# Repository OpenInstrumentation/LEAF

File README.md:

# LEAF
Logger for Environmental and Atmospheric Factors

CC-BY-SA 2019, A. Matheny, P. Marchetto, J. Powell, A. Rechner, J-y. Chuah, and S. Pierce

BoM: https://docs.google.com/spreadsheets/d/e/2PACX-1vQ8v-ukr38iTDn-cAedqp6OXnIay0lwoVsFbz_EMlWamA66PgREalaegVoSEzRlPvawVt73zznOhLpU/pubhtml or any of the BoM files above.

# Purpose
The LEAF is designed to be a modular sensing system, capable of measuring meteorological, hydrological, and other environmental parameters. In the design detailed in this repository, it was used to measure canopy throughfall of rain, soil moisture, and microclimate meteorological parameters, along with branch movement in the same tree the throughfall measurements were being made in.

# Files
The files in this repository are what's needed to program the different nodes of the sensing system network. The ground .ino file is different from the branches because it measures soil moisture as well; both of the .ino files are designed to be uploaded via Particle's online IDE at http://build.particle.io/. The catalog file includes all of the different items as priced at the time of the build, and the BoM includes direct links to them. The deployment file shows roughly what the initial instance looked like in its first deployment. The .brd and .sch files are Eagle board and schematic files, respectively, used to make PCBs for the system.

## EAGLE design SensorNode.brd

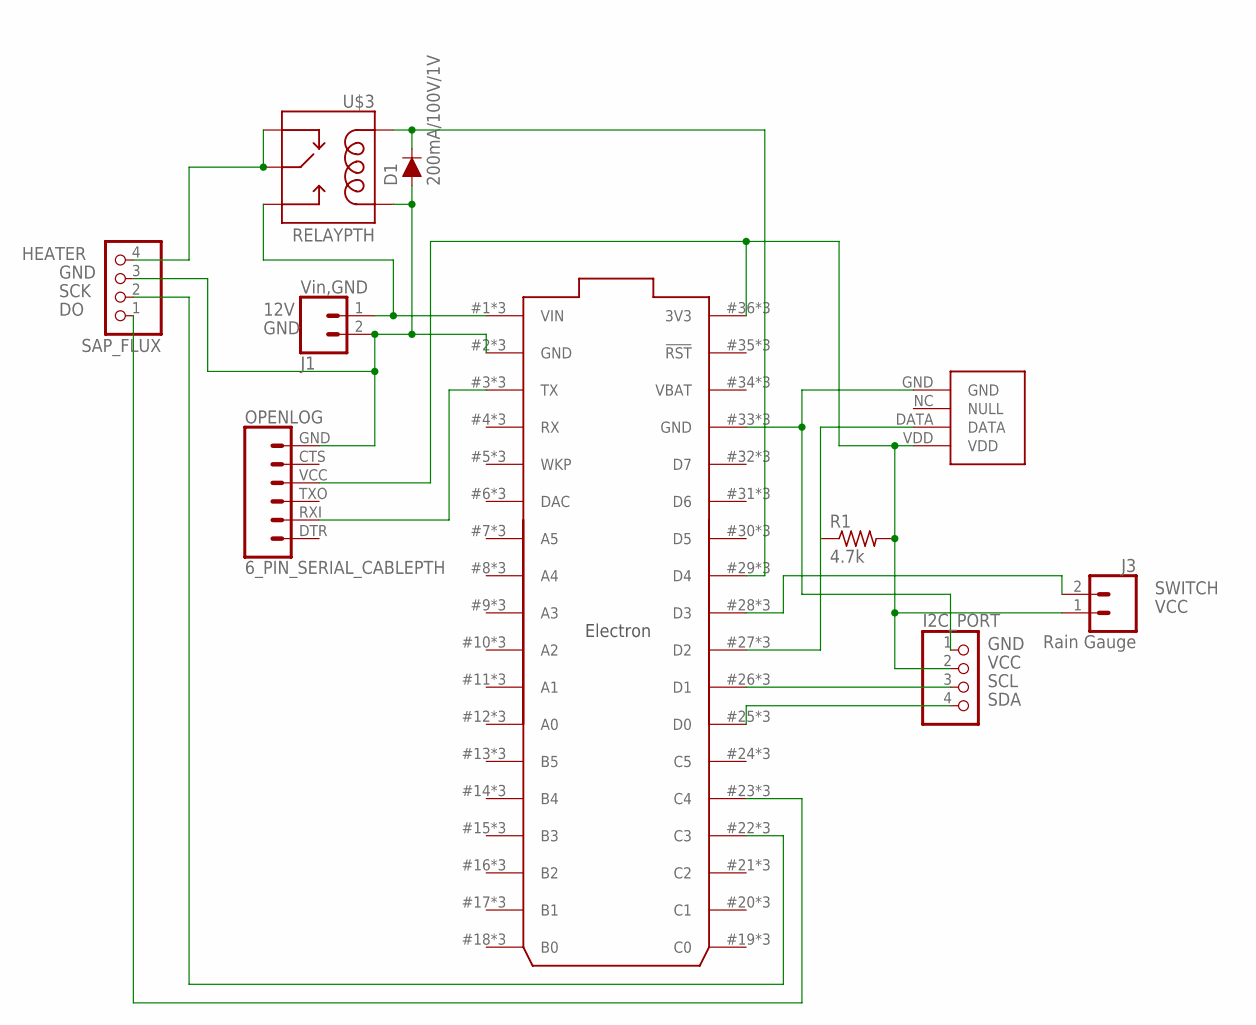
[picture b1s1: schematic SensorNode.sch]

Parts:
D1: 200mA/100V/1V; DIODE-1N4148
I2C_PORT: PINHD-1X4; 1X04
J1: Vin,GND; SCREWTERMINAL-3.5MM-2
J3: Rain Gauge; SCREWTERMINAL-3.5MM-2
OPENLOG: 6_PIN_SERIAL_CABLEPTH; FTDI_BASIC
R1: 4.7k; 0204/7
SAP_FLUX: PINHD-1X4; 1X04
U$1: ELECTRON_WITH_STACKABLE_HEADERS; ELECTRON_STACKABLE
U$2: DHT22
U$3: RELAYPTH; RELAY-G5Q

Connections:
12V: J1.1, U$1.1 (VIN), U$1.#1 (VIN), U$1.@1 (VIN), U$3.3 (NO)
DO: SAP_FLUX.1, U$1.23 (C4), U$1.#23 (C4), U$1.@23 (C4)
GND: D1.A, I2C_PORT.1, J1.2, OPENLOG.GND (6), SAP_FLUX.3, U$1.2 (GND), U$1.33 (GND), U$1.#2 (GND), U$1.#33 (GND), U$1.@2 (GND), U$1.@33 (GND), U$2.GND, U$3.1 (COIL2)
HEATER: SAP_FLUX.4, U$3.2 (MAIN), U$3.4 (NC)
unnamed: OPENLOG.RXI (2), U$1.3 (TX), U$1.#3 (TX), U$1.@3 (TX)
unnamed: U$1.27 (D2), U$1.#27 (D2), U$1.@27 (D2), U$2.DATA
unnamed: D1.C, U$1.29 (D4), U$1.#29 (D4), U$1.@29 (D4), U$3.5 (COIL1)
SCK: SAP_FLUX.2, U$1.22 (C3), U$1.#22 (C3), U$1.@22 (C3)
SCL: I2C_PORT.3, U$1.26 (D1), U$1.#26 (D1), U$1.@26 (D1)
SDA: I2C_PORT.4, U$1.25 (D0), U$1.#25 (D0), U$1.@25 (D0)
SWITCH: J3.2, U$1.28 (D3), U$1.#28 (D3), U$1.@28 (D3)
VBAT: U$1.34 (VBAT), U$1.#34 (VBAT), U$1.@34 (VBAT)
VCC: I2C_PORT.2, J3.1, OPENLOG.VCC (4), R1.2, U$1.36 (3V3), U$1.#36 (3V3), U$1.@36 (3V3), U$2.VDD

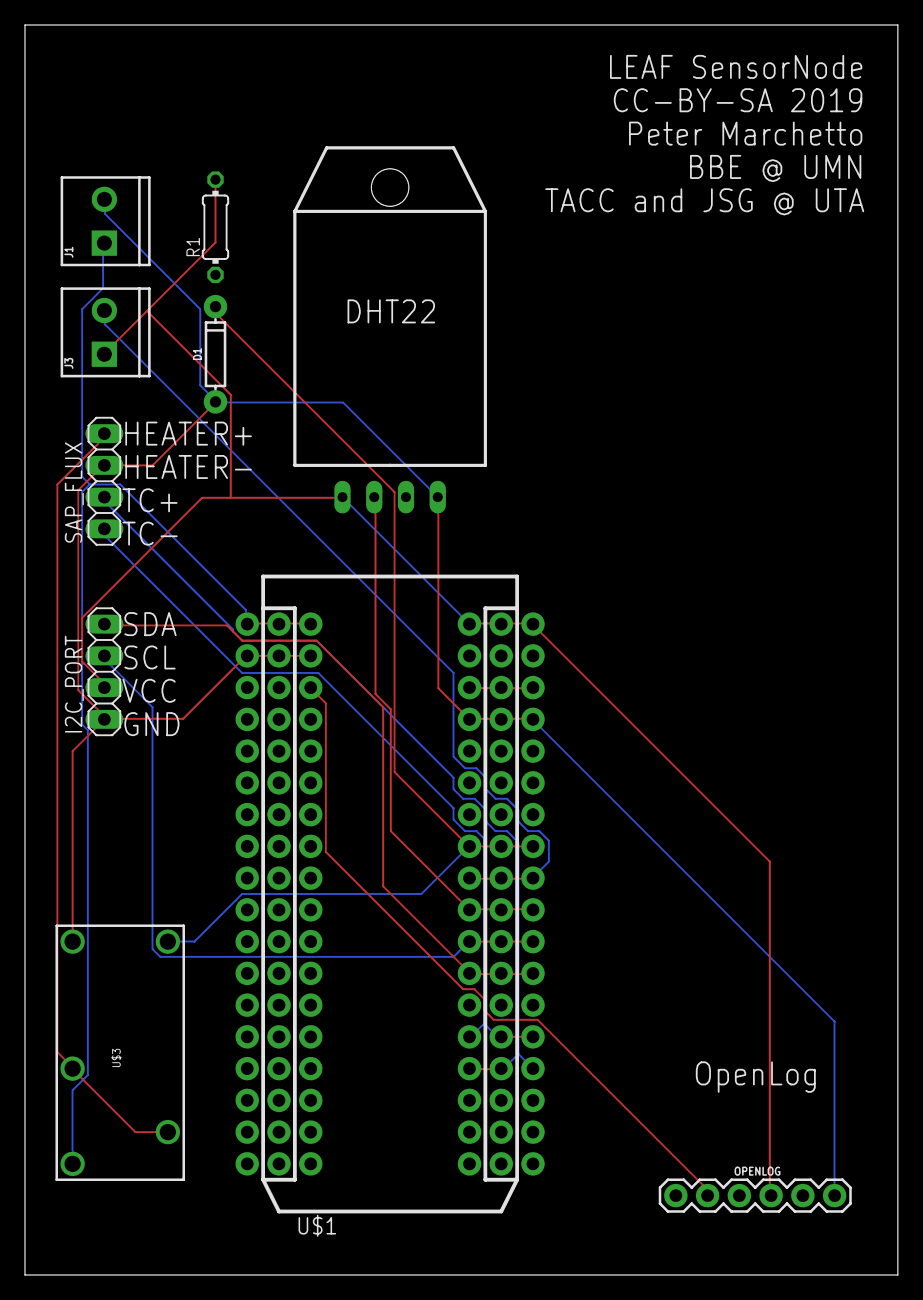
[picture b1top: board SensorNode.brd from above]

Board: 2 copper layers, 69.8 x 100.0 mm, 10 parts (0 on the bottom side), 13 nets.

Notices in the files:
parts and their libraries:
SparkFun-DiscreteSemi: Licensing: Creative Commons ShareAlike 4.0 International - https://creativecommons.org/licenses/by-sa/4.0
Particle-Devices: Licensing: Designed by Particle.
